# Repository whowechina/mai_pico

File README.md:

# Mai Pico - Maimai Style Mini Controller
[点这里可以切换到中文版](README_CN.md)

**Features:**
* Made with a 15.6 inch portable screen.
* Arcade-like experience.
* Dual-player is possible.
* Built-in AIME support.
* All source files open.

Thanks to many respectful guys/companies who made their tools or materials free or open source (KiCad, OnShape, InkScape, Raspberry things, JLCPCB), and also:
* RP_Silicon_KiCad: https://github.com/HeadBoffin/RP_Silicon_KiCad
* Switch_Keyboard_Kailh: https://github.com/kiswitch/keyswitch-kicad-library
* Type-C: https://github.com/ai03-2725/Type-C.pretty
* Mai2Touch: https://github.com/Sucareto/Mai2Touch

## Notes
This project is the most complex one among all my projects.
* It needs a custom etched ITO glass and a portable display.
* Heavily depends on 3D printing.
* Requires skills to solder tiny components.
* Requires many other DIY hands-on skills.
* The IO PCB is still in prototype state, it works, but the layout and connectors are not perfect. You may need to solder directly from Pi Pico's pins. I'm just too lazy to release a new version.
* I didn't design the housing, so it's your job to make it look nice and structually stable, follow your imagination and taste.

## About the License
It's CC-NC. So DIY for yourself and for your friend for free, don't make money from it. And plagiarism that doesn’t even dare to mention the original author is not acceptable. Plase note that pooling orders and group buying for raw materials is acceptable. Selling off any leftover components without profit is also acceptable.

If you're interested in buying from me or some kind of commercial use, please contact me (Discord, QQ group, Wechat group or leave your contact in issue section).

## My Discord Invitation
https://discord.gg/M8f2PPQFEA

## My Other Projects
You can check out my other cool projects.

* Popn Pico: https://github.com/whowechina/popn_pico
* IIDX Pico: https://github.com/whowechina/iidx_pico
* IIDX Teeny: https://github.com/whowechina/iidx_teeny
* Chu Pico: https://github.com/whowechina/chu_pico
* Mai Pico: https://github.com/whowechina/mai_pico
* Diva Pico: https://github.com/whowechina/diva_pico
* AIC Pico: https://github.com/whowechina/aic_pico
* Groove Pico: https://github.com/whowechina/groove_pico
* Geki Pico: https://github.com/whowechina/geki_pico
* Musec Pico: https://github.com/whowechina/musec_pico
* Ju Pico: https://github.com/whowechina/ju_pico
* Bishi Pico: https://github.com/whowechina/bishi_pico
* Bishi Pico: https://github.com/whowechina/nos_pico

## **Disclaimer** ##
I made this project in my personal time without any sponsorship. I will continue to improve the project. I have done my best to ensure that everything is accurate and functional, there's always a chance that mistakes may occur. I cannot be held responsible for any loss of your time or money that may result from using this open source project. Thank you for your understanding.

## Builds Gallery
Before we start, I want to encourage you with some hobbyist builds.

### **Lavide's Build**
  Lavide made a nice compact all-in-one Mai Pico cab!  

### **Romper's Build**
  Romper made a full-size con using Mai Pico's touch design.  
    
  Check out his build guide here.  
  https://github.com/ir0nq/maimai-homemade-controller

### **imfrea's Build**
  imfrea designed a nice-looking and inexpensive acrylic housing for Mai Pico.  
    
  You can download the acrylic case designs from his fork of Mai Pico here.  
  https://github.com/imfrea/mai_pico

### ***IlIIllllIlIIlll's Build**
  IlIIllllIlIIlll made another nice and compact housing.  
       
  Thanks to his/her contribution, you can download the design files directly from this repository. It's located at `Production\3rdparty\IlIIllllIlIIlll_housing.zip`. The panel can be cut from PP or acrylic sheets, and other parts can be 3D printed. Plase note that this design is also not for commercial use.

## HOW TO BUILD
### PCB
* Go JLCPCB and make order with the gerber zip file (latest `Production\PCB\mai_io_v*.zip` and `Production\PCB\mai_button_v*.zip`), regular FR-4 board, 1.6mm thickness. You need 1x io PCB and 8x button PCBs for one Mai Pico con.  
  
* 1x Rasberry Pico Pi Pico or Pico W.  
  https://www.raspberrypi.com/products/raspberry-pi-pico
  Becareful of 3 pins that are at the other side, they're difficult to solder and may leave air bubbles.  
  
* 1x USB Type-C socket (918-418K2023S40001 or KH-TYPE-C-16P)
* 2x 0603 5.1kohm resistors (R20, R21) for USB. If you plan to use the native USB socket on the Pi Pico directly, then the Type-C socket and resistors can be omitted, making the soldering much simpler.
* 3x MPR121 modules, there're many types in the market, choose ones like this.  
  https://www.sparkfun.com/products/retired/9695  
  Before solder MP121 module to the main PCB board, remember to use a knife to **cut (unshort) the tiny trace that connects ADDR to the GND**. Please be careful not to cut more than necessary.  
  
* Leave U5, U6, U7 area discrete components empty as we're using MPR121 module, not the chip. Please note that these components are removed in the newer version board.
* 1x SN74LV1T34DBVR (SOT-23-5) level shifter (U8), if you can't find one, just use a 0603 10ohm resistor (R4) as an alternative. In newer version board, it's removed.  
  https://www.lcsc.com/product-detail/Buffer-Driver-Transceiver_Texas-Instruments-SN74LV1T34DBVR_C100024.html
* 4x 0603 1uF (0.1~1uF all fine) capacitors (C1, C2, C3, C7), OPTIONAL, recommended. Please note that some are removed in the newer version board.
* 16x WS2812B-3528 RGB LEDs (each button needs two).
* 8x Kailh Choc v1 key switches, linear, 30gf to 45gf ones.  
  https://www.kailhswitch.com/mechanical-keyboard-switches/low-profile-key-switches/burnt-orange-switch.html
* 1x PN532 NFC module and some thin wires, only needed if you want AIME.  
  https://www.elechouse.com/product/pn532-nfc-rfid-module-v4/  
  You need to solder it to the same I2C as the MPR121 (GPIO 6 and 7).
* These are only for buttons with optical sensors.
  * 8x 0603 220ohm resistors (R1, R2, R3, R4, R5, R6, R7, R8), they're current limiter.
  * 8x 0603 5.1kohm resistors (R10, R11, R12, R13, R14, R15, R16), they're pull-up resistors. There's chance you don't need them, you can try without them first.

### ITO Glass
* Find a service to make custom etching ITO coated glass. The AutoCAD file is `Production\CAD\mai_pico_ito_v*.dwg`. Use 2mm thickness, 10-20ohm sheet resistance ITO coated glass.
  
* The ITO coated glass is connected to the IO PCB by "zebra cable" (1.6mm pitch: 0.8mm black part and 0.8mm clear part). A silicon heater head at 200°C is used to stick the zebra cable to the gold finger part of PCB and ITO coated glass. The formal name of this cable is "Heat Seal Connector".  
  
* Custom ITO coated glass is relatively expensive, but ours is small, so it's not like arcade-size expensive. This is the shop I ordered the ITO glass. The minimal batch is around 5 pieces. But they provide service only in China as far as I know.  
  https://shop378788148.taobao.com/?spm=2013.1.1000126.2.305e16c4LFf1GW

### Button Ring
* Print out the 8x set of base, link, button and cover from `Production\3DPrint\mai_*.stl`.
* Buy 8x 2mm (diameter) * 40mm (length) steel shafts, they're used as the button hinge.
* Here's how to assemble them, hinge shaft and components on PCB are not shown in this rendered image.  
  
* Here's how I assembled the ring. Please note that wiring for the button switches is missing in these pictures.
  * All discrete components ready.  
    
  * Solder the button PCB first.  
    
  * Button PCBs are daisy-chained using short and soft 3-wire cable, they're G, IN/OUT, V (GND, Signal In/Out and VCC respectively). RGB signal goes in from "IN" and goes out to the next LED through "OUT". The "Btn" button signal pins are not soldered yet, you can later wire them. Don't worry about the order of button GPIOs, because they can be remapped through command line interface.    
    
  * You need 3M5423 UHMW film tape (or similar hard and super-smooth PTFE tape with 0.2-0.3 thickness). It is to lubricate the button surface that touches the keyswitch.  
    
  * Assemble the 3D printed parts together with the PCBs.  
    
  * Use shaft to expand the support holes a little bit, and apply some keyboard switch lubricant such as Krytox 205G0 to make the shaft super smooth.  
    
  * Each `link` needs 8x M2*4mm screws to connect two `base`s together.  
    
  * Install the cover, each needs 2x M2*5mm screws.  

### Portable Display
  * Resolution: 1920*1080, size: 15.6inch, refresh rate: 120Hz (recommended) or 60Hz, built-in speakers.
  * They're easy to find. Choose cheap or even tiny-flawed ones, they're much cheaper and work just fine.
  * There're 2 types of driver board, one is micro-HDMI only and the other supports type-C display (for convenient Nintendo Switch connection). They're both OK.  
  https://www.amazon.com/s?k=portable+display+15.6+120hz&s=price-asc-rank&crid=1CCA2EAYLZDBE&qid=1697276847&sprefix=portable+display+15.6+120hz%2Caps%2C387&ref=sr_st_price-asc-rank&ds=v1%3AqoS0mks05q225yuL8reh50fEEBkTZ583nMPEZJwjXAk

### Glue Things Together
  * I use 3M VHB tape (0.5mm or 1mm thickness) to stick the button ring, the ITO glass and the monitor together.
  * Only use a little tape, I use 4 small pieces to stick ITO glass to the display and another 4 small pieces to stick button ring to the ITO glass.
  * Don't apply the tape on the traces of the ITO glass, you can see the traces or pads at certain angle.

### Housing
  * It's your job to design it and make it look nice.

### Firmware
* UF2 file is in `Production\Firmware` folder.
* For the new build, hold the BOOTSEL button while connect the USB to a PC, there will be a disk named "RPI-RP2" showed up. Drag the UF2 firmware binary file into it. That's it.
* LED and Touch protocols are implemented following Sucareto's research at https://github.com/Sucareto/Mai2Touch.
* It has a command line to do configuration. You can use this Web Serial Terminal to connect to the USB serial port of the Mai Pico. (`?` to display help message.)  
  https://googlechromelabs.github.io/serial-terminal/  
  
   * Please note that when you click "Connect" button, you'll actually see the name of each port.  
   
* Button GPIOs can be remapped using `gpio` command. Firmware supports 8 main buttons on the ring and 4 auxiliary buttons (Test, Service, Navigate and Coin).
* Touch keys can be remapped using `touch` command. For people who's using Mai Pico to drive a custom ITO film or a ITO glass, this command will be very useful. For example:
  * `touch` with no parameter is to detect touched keys.
  * `touch 1 9 E6` is to set the second MPR121's electrode 9 to key "E6". Key name of "XX" means "Not Connected".
* Daisy chained RGB LED numbers for each button can be assigned using `rgb` command.
* LED brightness can be adjusted by `level` command.
* There are MPR121 parameter tuning and sensitive settings, explore them yourself.
* It implements 3 COM ports, one is for command line and the other two are for LED and Touch. By issuing `whoami` to the command line, each COM port will print their identities.
* Button signal is sent to the host by HID Joystick or HID NKRO (keyboard). There're two set of NKRO keymaps, use `hid <joy|key1|key2>` to switch between them. In NKRO mode, key mappings are:
  * key1: `WEDCXZAQ`-Ring Buttons, `3`-Select
  * key2 (Numpad): `89632147`-Ring Buttons, `*`-Select
  * Above two sets both have: `F1`-Test `F2`-Service `F3`-Coin
* `factory` to reset to default. When there's a firmware update, the old configuration may become corrupted, you can reset configuration, then re-plug the controller.

## CAD Source File
I'm using OnShape free subscription. It's powerful but it can't archive original designs to local, so I can only share the link here. STL/DXF/DWG files are exported from this online document.  
https://cad.onshape.com/documents/d8b39d27c9cb7990d9ce4d46/w/2c1baa71e391bfd1246f122b/e/f87f0f1c373fe2186ddc5c9c?renderMode=0&uiState=652a665608b4e07137e3861a

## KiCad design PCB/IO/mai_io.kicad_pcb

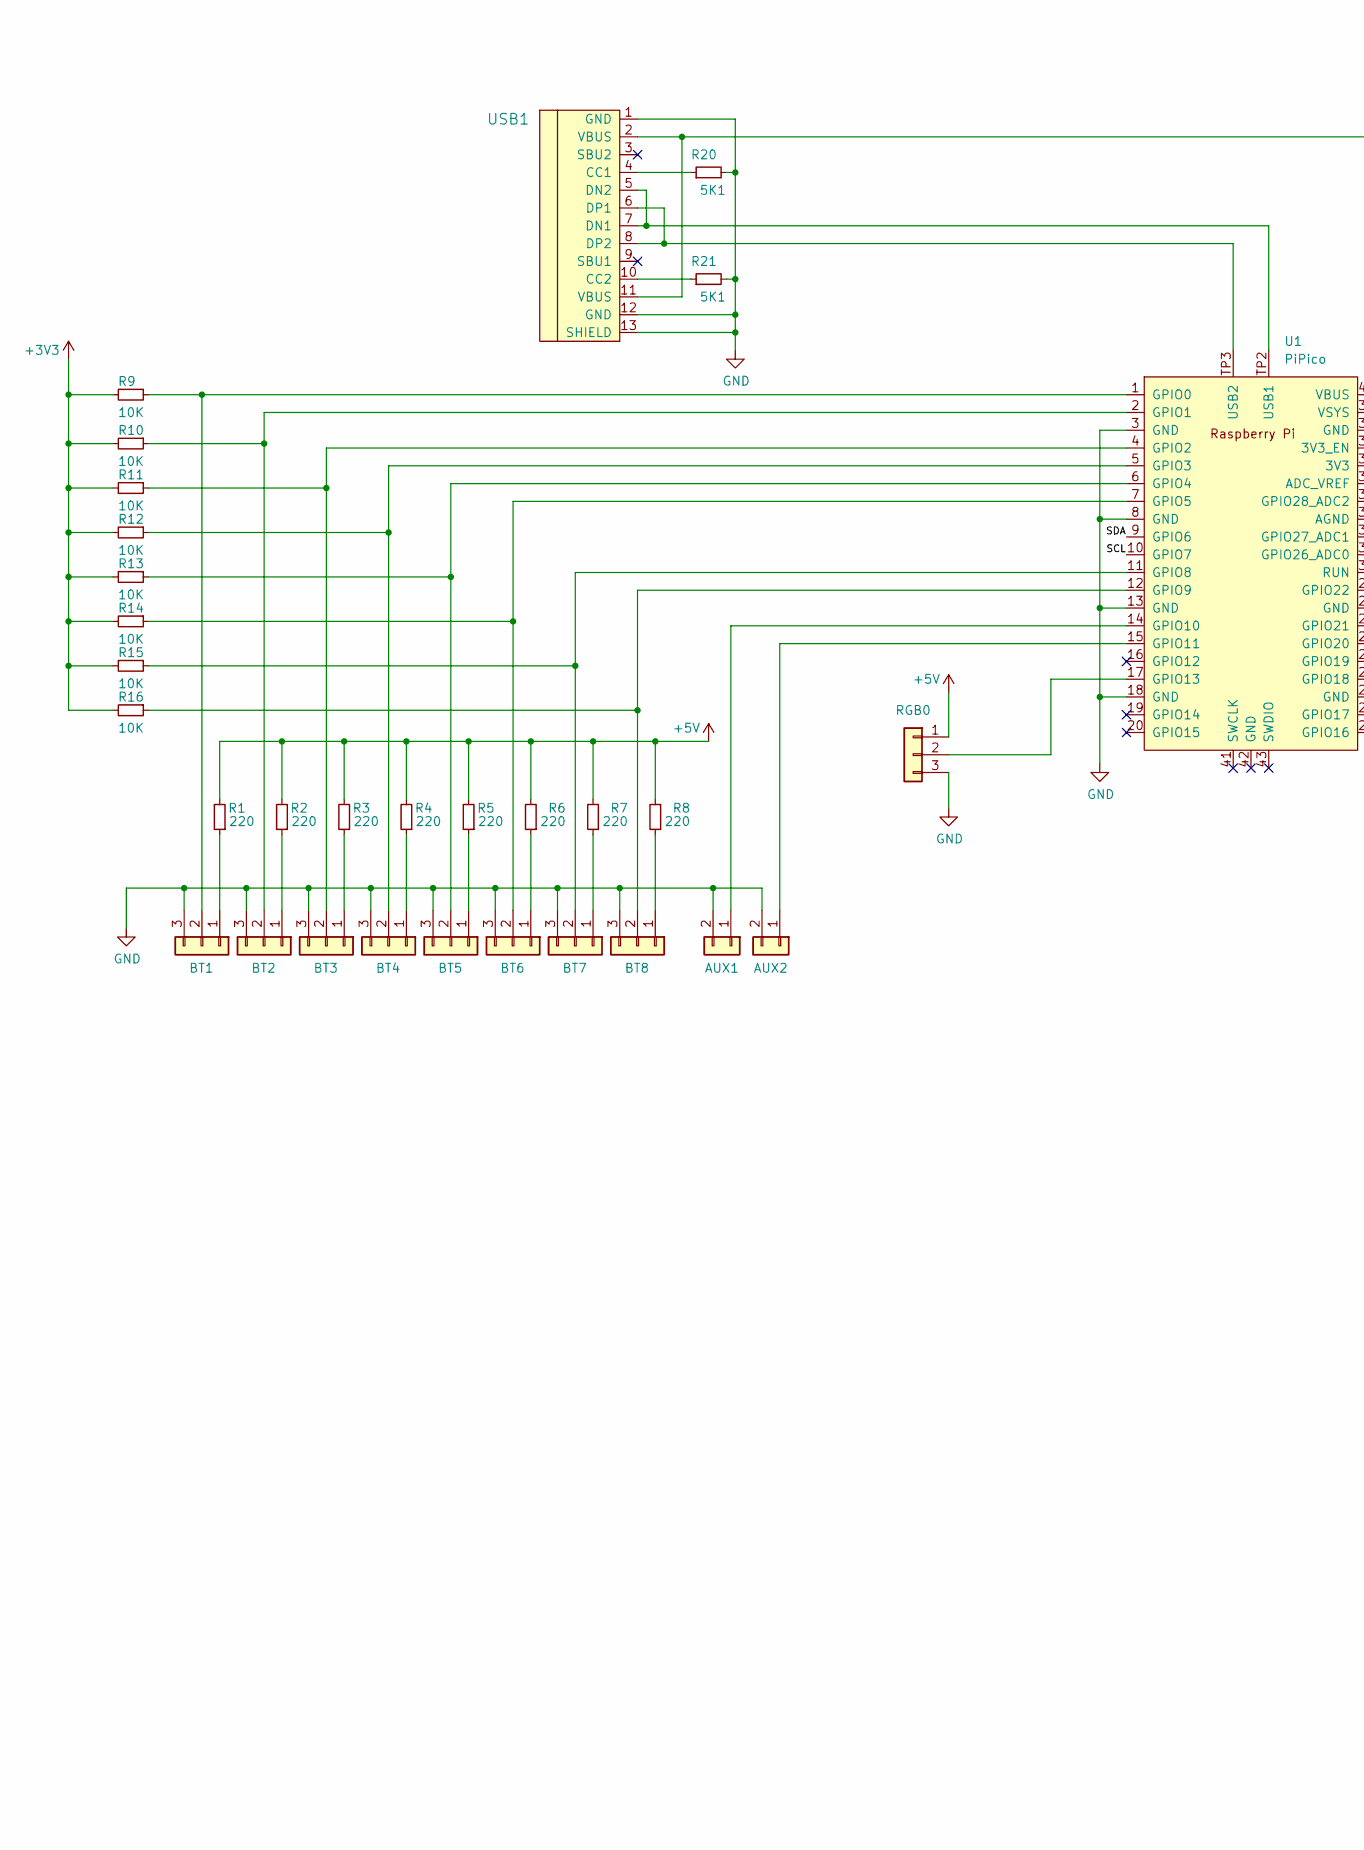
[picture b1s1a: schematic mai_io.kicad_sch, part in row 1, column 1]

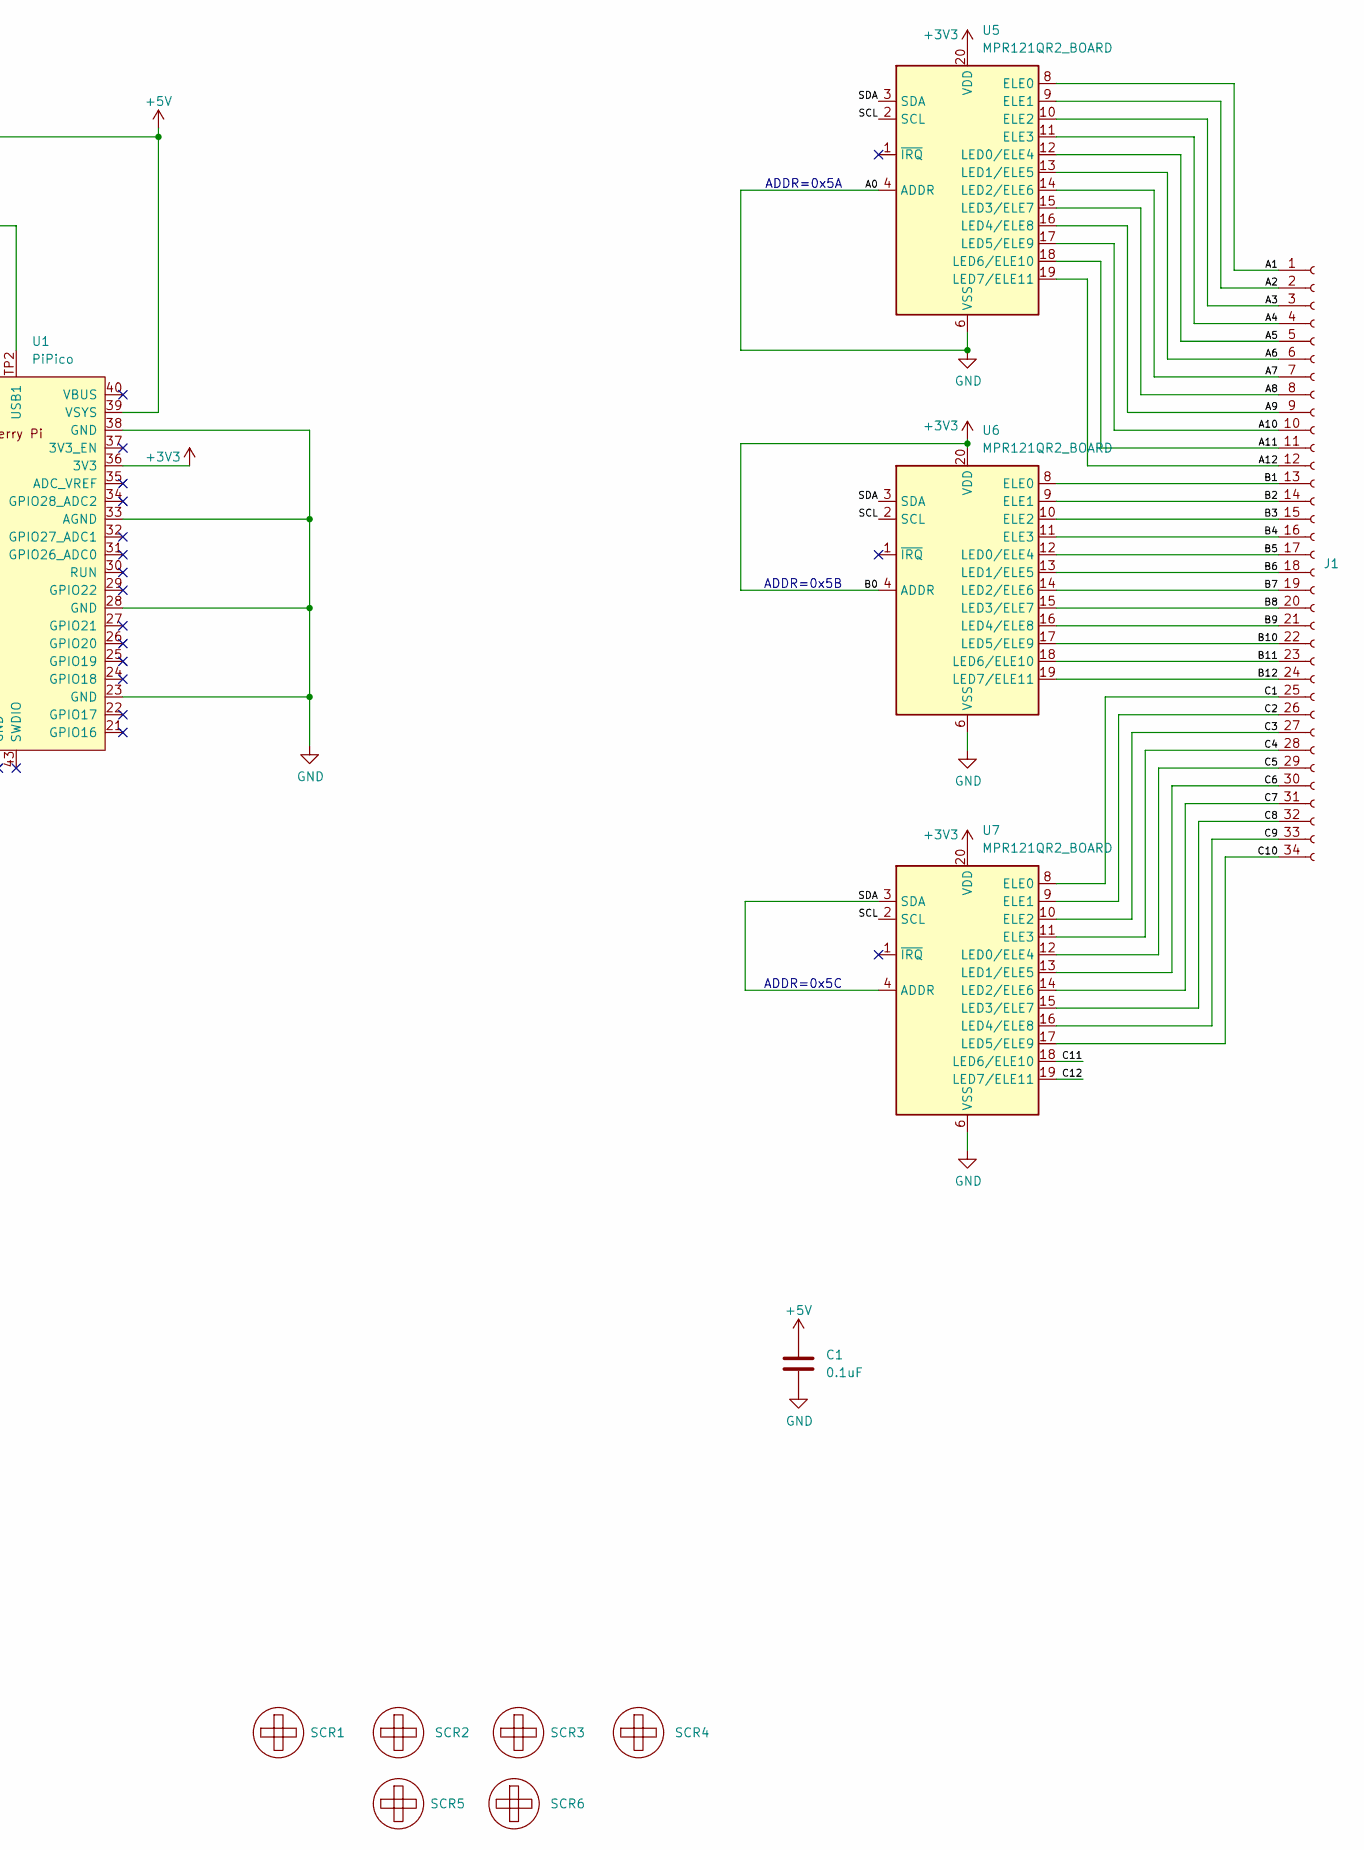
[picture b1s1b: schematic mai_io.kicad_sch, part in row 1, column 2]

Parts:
AUX1, AUX2: Conn_01x02; JST_EH_B2B-EH-A_1x02_P2.50mm_Vertical
BT1, BT2, BT3, BT4, BT5, BT6, BT7, BT8: Conn_01x03; JST_EH_B3B-EH-A_1x03_P2.50mm_Vertical
C1: 0.1uF; C_0603_1608Metric_Pad1.08x0.95mm_HandSolder
J1: Conn_01x34_Female; MaiTouch_Conn34
R1, R2, R3, R4, R5, R6, R7, R8: 220; R_0603_1608Metric_Pad0.98x0.95mm_HandSolder; LCSC C23186
R9, R10, R11, R12, R13, R14, R15, R16: 10K; R_0603_1608Metric_Pad0.98x0.95mm_HandSolder; LCSC C23186
R20, R21: 5K1; R_0603_1608Metric_Pad0.98x0.95mm_HandSolder; LCSC C23186
RGB0: Conn_01x03; JST_EH_B3B-EH-A_1x03_P2.50mm_Vertical
SCR1, SCR2, SCR3, SCR4, SCR5, SCR6: ScrewHole; MountingHole_3.2mm_M3
U1: PiPico; RPi_Pico_SMD_Pins
U5, U6, U7: MPR121QR2_BOARD; MPR121_BOARD
USB1: U262-161N-4BVC11; HRO-TYPE-C-31-M-12-Assembly; LCSC C319148

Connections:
+3V3: R9.2, R10.2, R11.2, R12.2, R13.2, R14.2, R15.2, R16.2, U1.36 (3V3), U5.20 (VDD), U6.4 (ADDR), U6.20 (VDD), U7.20 (VDD)
+5V: C1.1, R1.2, R2.2, R3.2, R4.2, R5.2, R6.2, R7.2, R8.2, RGB0.1, U1.39 (VSYS), USB1.2 (VBUS), USB1.11 (VBUS)
/A1: J1.1, U5.8 (ELE0)
/A2: J1.2, U5.9 (ELE1)
/A3: J1.3, U5.10 (ELE2)
/A4: J1.4, U5.11 (ELE3)
/A5: J1.5, U5.12 (LED0/ELE4)
/A6: J1.6, U5.13 (LED1/ELE5)
/A7: J1.7, U5.14 (LED2/ELE6)
/A8: J1.8, U5.15 (LED3/ELE7)
/A9: J1.9, U5.16 (LED4/ELE8)
/A10: J1.10, U5.17 (LED5/ELE9)
/A11: J1.11, U5.18 (LED6/ELE10)
/A12: J1.12, U5.19 (LED7/ELE11)
/B1: J1.13, U6.8 (ELE0)
/B2: J1.14, U6.9 (ELE1)
/B3: J1.15, U6.10 (ELE2)
/B4: J1.16, U6.11 (ELE3)
/B5: J1.17, U6.12 (LED0/ELE4)
/B6: J1.18, U6.13 (LED1/ELE5)
/B7: J1.19, U6.14 (LED2/ELE6)
/B8: J1.20, U6.15 (LED3/ELE7)
/B9: J1.21, U6.16 (LED4/ELE8)
/B10: J1.22, U6.17 (LED5/ELE9)
/B11: J1.23, U6.18 (LED6/ELE10)
/B12: J1.24, U6.19 (LED7/ELE11)
/C1: J1.25, U7.8 (ELE0)
/C2: J1.26, U7.9 (ELE1)
/C3: J1.27, U7.10 (ELE2)
/C4: J1.28, U7.11 (ELE3)
/C5: J1.29, U7.12 (LED0/ELE4)
/C6: J1.30, U7.13 (LED1/ELE5)
/C7: J1.31, U7.14 (LED2/ELE6)
/C8: J1.32, U7.15 (LED3/ELE7)
/C9: J1.33, U7.16 (LED4/ELE8)
/C10: J1.34, U7.17 (LED5/ELE9)
/C11: U7.18 (LED6/ELE10)
/C12: U7.19 (LED7/ELE11)
/SCL: U1.10 (GPIO7), U5.2 (SCL), U6.2 (SCL), U7.2 (SCL)
/SDA: U1.9 (GPIO6), U5.3 (SDA), U6.3 (SDA), U7.3 (SDA), U7.4 (ADDR)
GND: AUX1.2, AUX2.2, BT1.3, BT2.3, BT3.3, BT4.3, BT5.3, BT6.3, BT7.3, BT8.3, C1.2, R20.2, R21.2, RGB0.3, U1.3 (GND), U1.8 (GND), U1.13 (GND), U1.18 (GND), U1.23 (GND), U1.28 (GND), U1.33 (AGND), U1.38 (GND), U5.4 (ADDR), U5.6 (VSS), U6.6 (VSS), U7.6 (VSS), USB1.1 (GND), USB1.12 (GND), USB1.13 (SHIELD)
unnamed: AUX1.1, U1.14 (GPIO10)
unnamed: AUX2.1, U1.15 (GPIO11)
unnamed: BT1.1, R1.1
unnamed: BT1.2, R9.1, U1.1 (GPIO0)
unnamed: BT2.1, R2.1
unnamed: BT2.2, R10.1, U1.2 (GPIO1)
unnamed: BT3.1, R3.1
unnamed: BT3.2, R11.1, U1.4 (GPIO2)
unnamed: BT4.1, R4.1
unnamed: BT4.2, R12.1, U1.5 (GPIO3)
unnamed: BT5.1, R5.1
unnamed: BT5.2, R13.1, U1.6 (GPIO4)
unnamed: BT6.1, R6.1
unnamed: BT6.2, R14.1, U1.7 (GPIO5)
unnamed: BT7.1, R7.1
unnamed: BT7.2, R15.1, U1.11 (GPIO8)
unnamed: BT8.1, R8.1
unnamed: BT8.2, R16.1, U1.12 (GPIO9)
unnamed: RGB0.2, U1.17 (GPIO13)
unnamed: U1.TP2 (USB1), USB1.5 (DN2), USB1.7 (DN1)
unnamed: U1.TP3 (USB2), USB1.6 (DP1), USB1.8 (DP2)
unnamed: R20.1, USB1.4 (CC1)
unnamed: R21.1, USB1.10 (CC2)

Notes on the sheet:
ADDR=0x5B
ADDR=0x5C
ADDR=0x5A

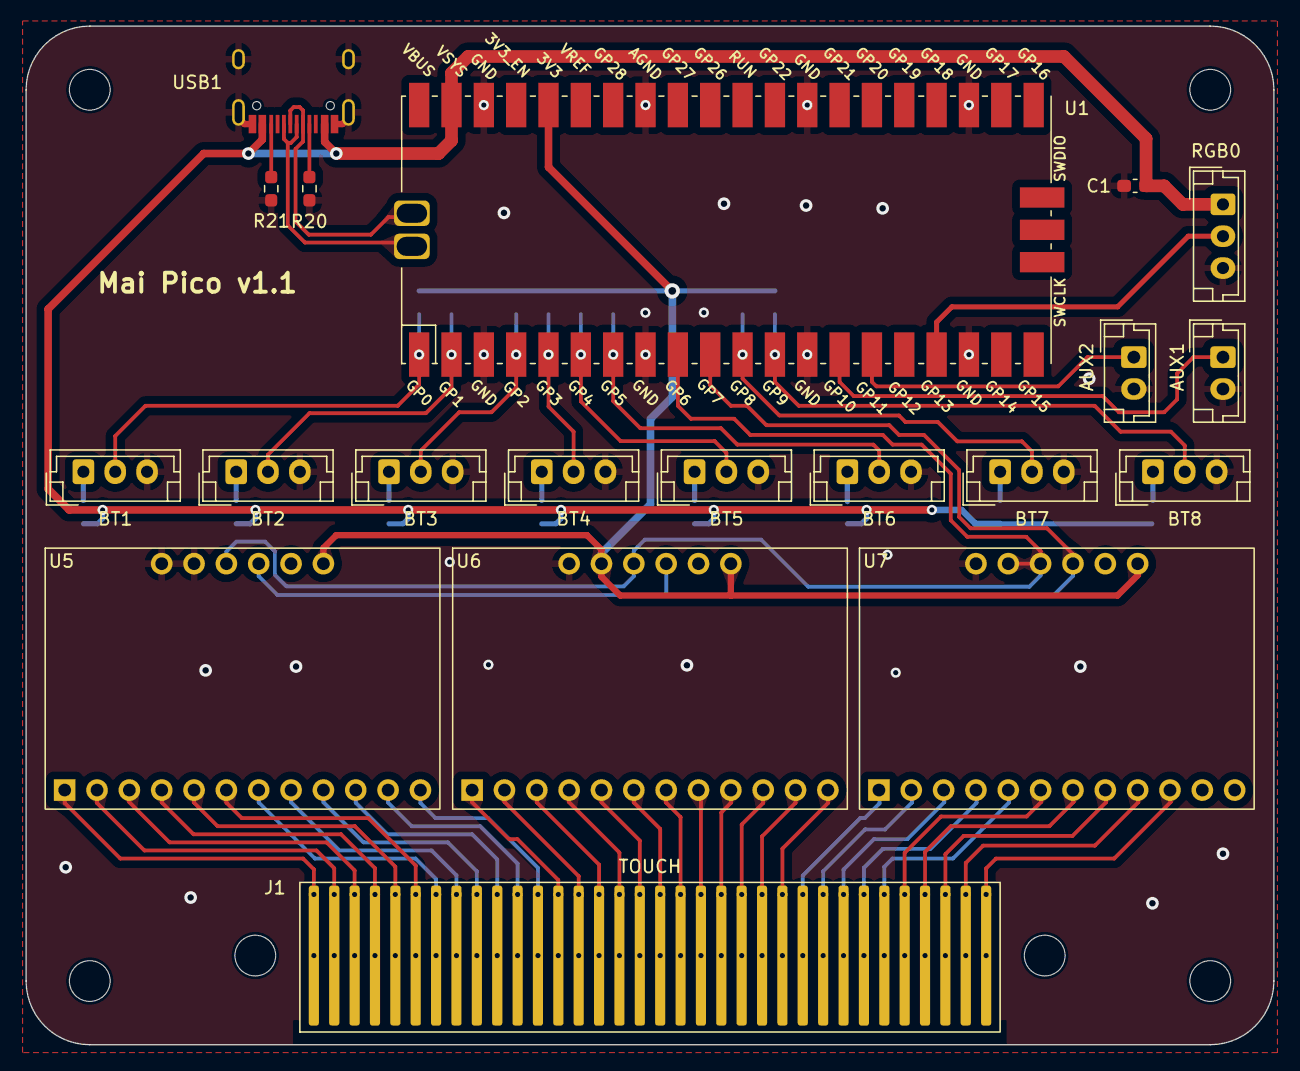
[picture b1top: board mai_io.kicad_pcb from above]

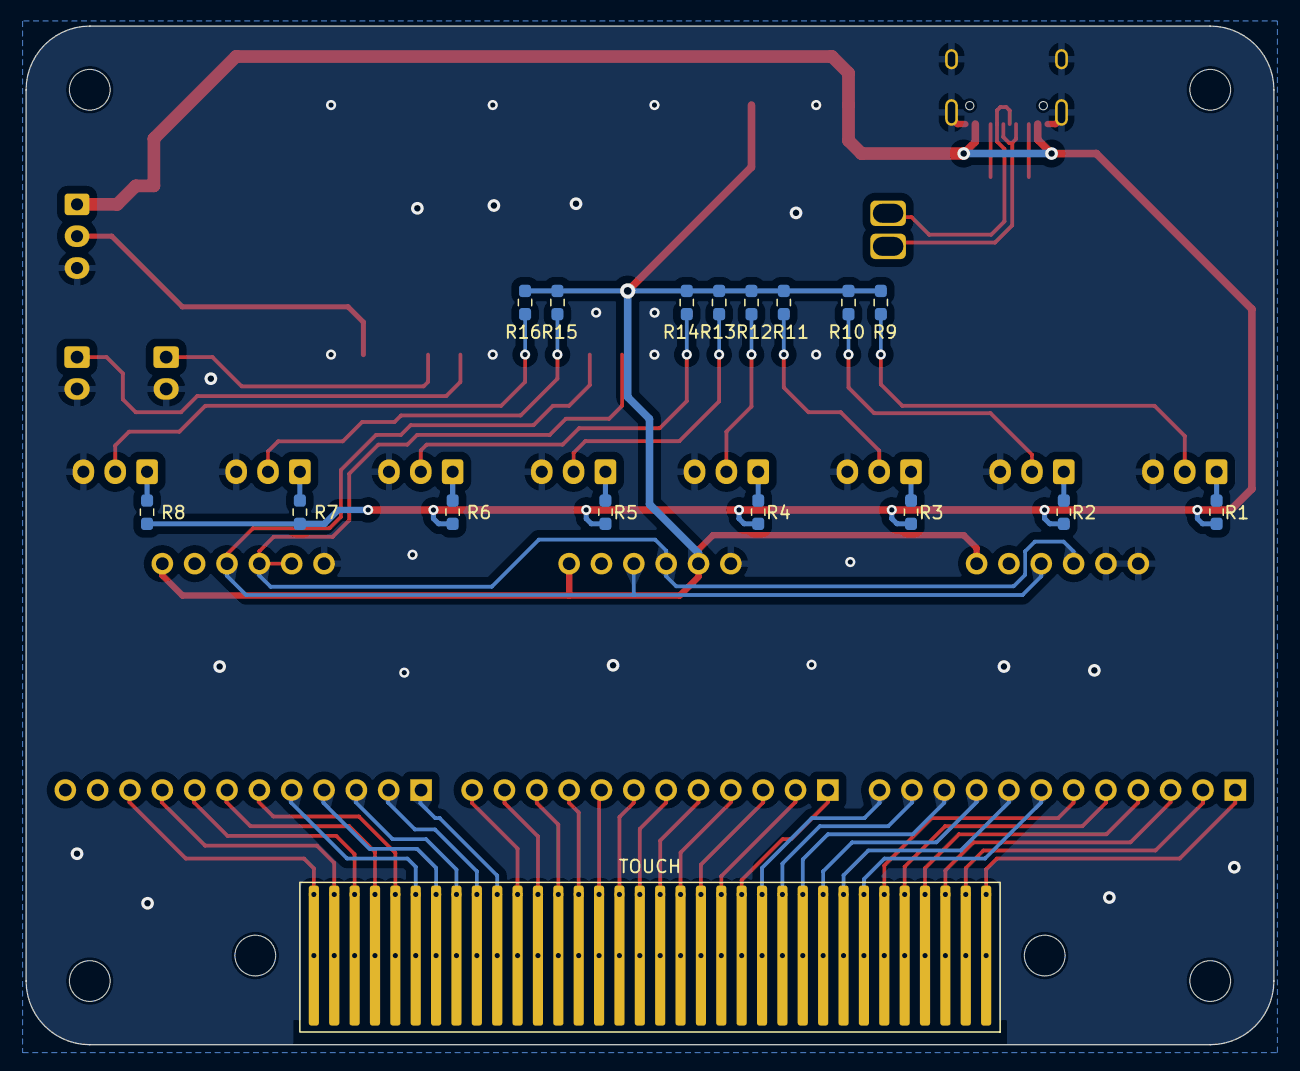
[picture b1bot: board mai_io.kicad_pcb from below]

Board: 2 copper layers, 98.0 x 80.0 mm, 42 parts (17 on the bottom side), 62 nets.

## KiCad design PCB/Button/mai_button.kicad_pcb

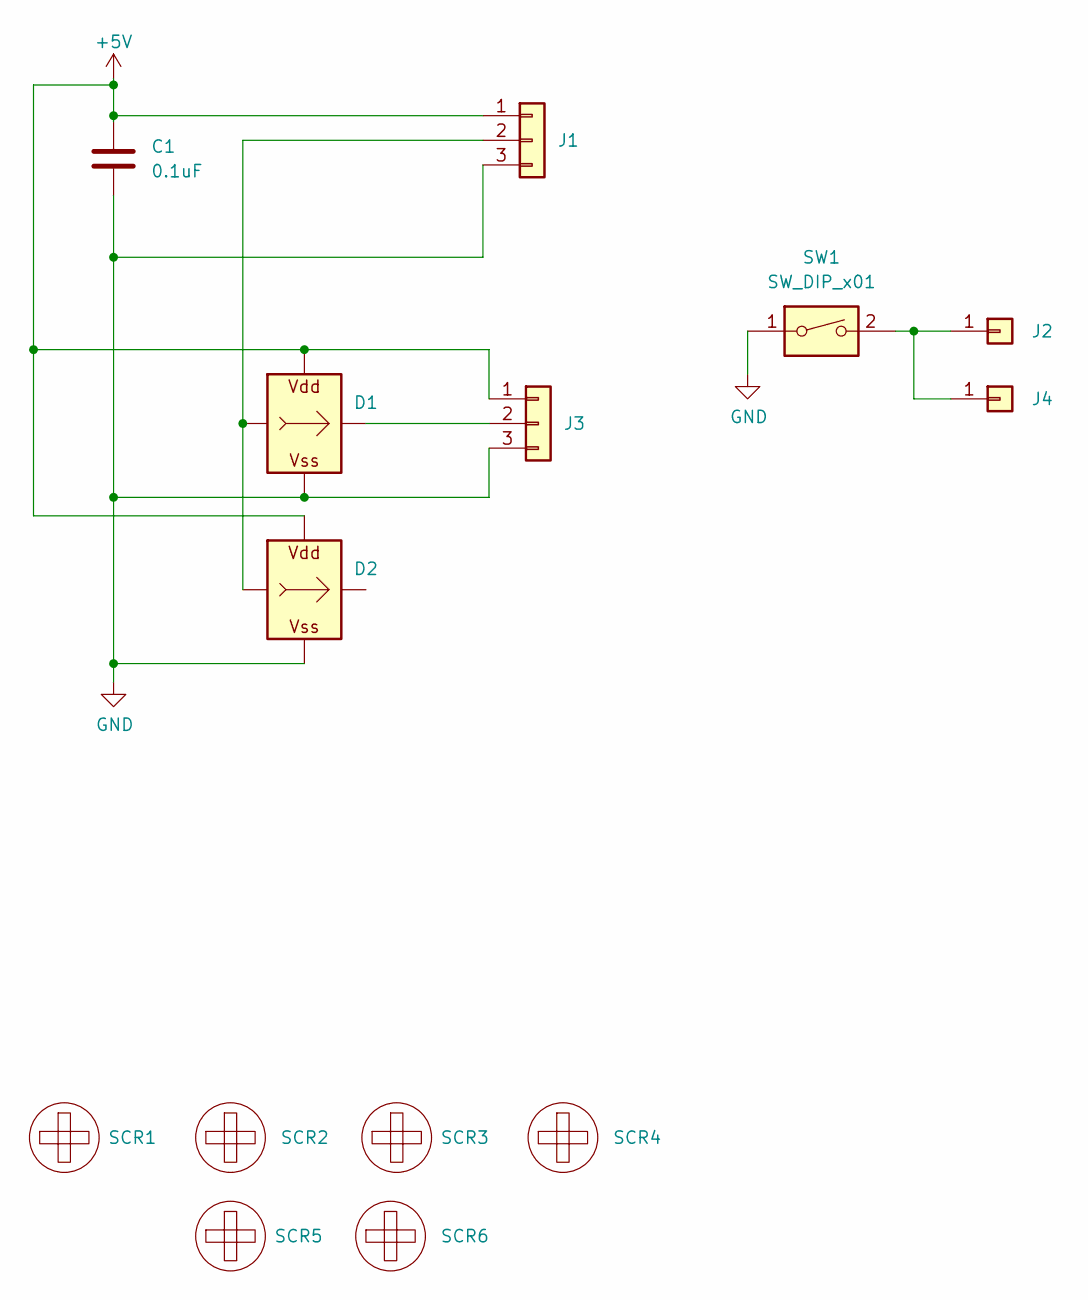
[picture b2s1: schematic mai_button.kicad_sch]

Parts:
C1: 0.1uF; C_0603_1608Metric_Pad1.08x0.95mm_HandSolder
D1, D2: WS2812B_Unified; WS2812B-2835
J1: RGB In; Solder_3P
J2, J4: Btn; Solder_1P
J3: RGB Out; Solder_3P
SCR1, SCR2, SCR3, SCR4: ScrewHole; Hole2.5
SCR5, SCR6: ScrewHole; Hole4.0
SW1: SW_DIP_x01; SW_Kailh_Choc_V1V2_1.00u_LED

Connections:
+5V: C1.1, D1.V (VDD), D2.V (VDD), J1.1, J3.1
GND: C1.2, D1.G (VSS), D2.G (VSS), J1.3, J3.3, SW1.1
unnamed: D1.I (In), D2.I (In), J1.2
unnamed: D1.O (Out), J3.2
unnamed: J2.1, J4.1, SW1.2

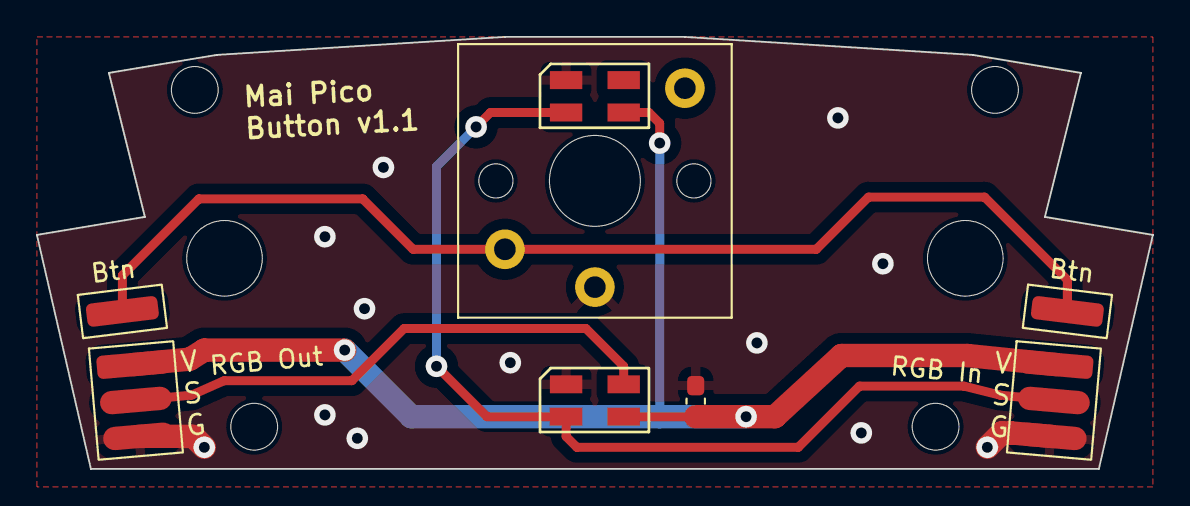
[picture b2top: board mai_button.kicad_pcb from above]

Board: 2 copper layers, 62.0 x 24.0 mm, 14 parts (0 on the bottom side), 5 nets.

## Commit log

2023-09-24 Firmware copied from chu pico
2023-09-29 Touch working, 3 CDC interfaces now
2023-09-30 Just playable now
2023-10-05 Custom HID mai2io DLL and 1KHz FPS
2023-10-10 Use pico's board id as USB SN
2023-10-11 SN number display
2023-10-11 Mai2io 2 con support (not working)
2023-10-12 Finally dual play working
2023-10-13 USB cleanup and nkro loss issue fixed.
2023-10-14 HID part optimization
2023-10-14 mio2io cleanup
2023-10-14 Removed mai2io dll
2023-10-14 3D print and CAD files update
2023-10-14 Remove duplicated dwg file
2023-10-14 USB descriptor string fix
2023-10-14 Readme and stuff for publish
2023-10-14 Small update on Readme
2023-10-14 Small typo fix
2023-10-15 Better touch baseline tracking
2023-11-05 Update command in CLI
2023-11-26 RGB LED number configurable (not tested)
2023-11-26 RGB num per button (if not work, use earlier UF2)
2023-12-08 Fixed touch update not fast enough issue
2023-12-09 Touch related command line finished
2023-12-09 Button via IO4 Support
2024-02-13 Button GPIOs can be re-assigned thru CLI
2024-02-14 Support fading, but not tested yet
2024-02-14 Some updates in README
2024-02-14 No wrap of thumbnails in README
2024-02-14 Fix fading delta time unit error
2024-02-16 Fix button read bug introduced in earlier commit
2024-02-16 Fading and gpio override finally work
2024-02-17 Extra buttons working in nkro mode: select/test/service/coin
2024-02-17 Fix LED bahavior
2024-02-18 Optimize Touch and LED log prints
2024-02-18 Update README a little bit
2024-02-25 Readme in Chinese
2024-02-25 IO4 output implemented and coin button working
2024-02-25 Just let coin count overflow
2024-02-25 Switch language easier
2024-02-25 Some wording update
2024-02-25 Some style fix
2024-03-03 Optimize README
2024-03-09 LED I/O can pass self-test
2024-03-09 Max electrode charge for better sense (test)
2024-03-23 Display sensor status in raw command
2024-04-04 Integrating AIC pico library
2024-04-05 AIME Support, not tested yet
2024-04-05 Experimental WebSerial File
2024-04-05 Web serial didn't work
2024-04-05 Better port naming
2024-04-05 Touch map in config
2024-04-05 Touch pad name interface
2024-04-05 Touch remap working.
2024-04-05 README update with touch and AIME support
2024-04-06 Optimize AIME commands
2024-04-13 Default touch map when update from old version
2024-04-28 Update to latest aic library
2024-04-28 Light effects when idle
2024-04-29 Suppress nkro when button stuck
2024-04-29 Validate gpio in gpio command
2024-04-30 Update to latest aic lib and fix aime random disconnect
2024-05-07 Button PCB update (v1.1)
2024-05-07 Minor button PCB update (so v1.11)
2024-05-18 Longer io timeout
2024-05-18 Put build time in help
2024-05-19 Cmake knows to update built time
2024-06-18 CLI welcome at connection
2024-06-18 Some warning cleanups
2024-06-18 Turn off light when exits rainbow mode
2024-06-18 Acitve-high button switches as a tweak options
2024-07-15 Cross-reference to new Groove Pico
2024-07-24 Builds Gallery
2024-07-24 Fix a typo
2024-07-24 Small wording update
2024-09-03 Upload "IlIIllllIlIIlll"'s design
2024-09-05 Thanks to some projects
2024-09-14 Feature: raw command with individual sensor readings and zone readings
2024-09-15 Fix: Use dependent buffer as readout buffer, then copy to readout array
2024-09-16 Revert: Remove accidential modification on board_defs
2024-09-16 Feature: Add map_raw_to_zones(), minor code structure modification
2024-09-16 Fix: Minor update on function signature
2024-09-17 Minor optimizations
2024-09-17 UF2 includes prettier output for raw command
2024-09-18 IO4 can be turned off (to live with official IO4 board)
2024-09-19 Fix error on cp command when building under windows
2024-10-02 Cross-reference and license part update
2024-10-18 Cross-reference and Discord invitation
2024-11-13 Cross-reference to Ju Pico
2024-11-23 Cross-reference
2024-11-29 Runtime touch reset with long-press COIN button
2024-11-29 Fix getchar return handling
2024-12-26 Longer IO timeout (5 min)
2024-12-26 Cross-link to bishi pico and readme re-arrangerment
2025-01-04 Slightly improve polling rate
2025-02-03 HID report change to edge triggering
2025-02-03 Sync to latest aic pico library
2025-02-03 Some typo fix
2025-02-03 Cab lights and aime reader lights
2025-02-03 Fix MPR121 filter setting bug
2025-03-18 Debug command to hide logs
2025-04-04 Cross-reference to Nos Pico
2025-04-06 Period HID report to pass self-test
2025-04-18 Async nfc ops for aime ops during gameplay
2025-06-30 IO board v1.1 (better support for arcade buttons and simplified)
2025-07-06 Fix touch update
2025-07-06 Add mpr121 debug
2025-07-06 Add build gitignore
2025-07-06 Unbound sense limit
2025-07-06 FIx limits
2025-07-06 Fix mpr121 logic
2025-07-06 Fix sense input logic
2025-08-03 Fix io4 button mapping
2025-08-03 UF2 (fixed io4 mapping and sense mapping)
